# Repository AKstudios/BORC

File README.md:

# BORC
Battery-Operated Radiator Control

A low-power automatic radiator control that is designed to retrofit on steam radiators that use Honeywell's T104A1040 Zone Valve Operator
uses LowPowerLab's [DualOptiboot](https://github.com/LowPowerLab/DualOptiboot) bootloader for the ATmega1284P.

This repo contains:
- PCB design files and schematic for control board, power board and LED board for the BORC.
- Firmware for a low-power radiator control node
- Logger script to get real-time current data from the BORC

---

### Logger script

The [logger script](https://github.com/AKstudios/BORC/blob/dev/logger/logger.py) enables capturing current usage data over the serial port on the BORC.

#### Prerequisites:
- [Pyserial](https://pypi.org/project/pyserial/)

#### Run:
Run the script using the following command over a command line interface:

```
python logger.py -c COM15 -n filename
```
(change COM port number and filename as needed)

#### Tips:
- The script automatically adds the .csv extension to the filename, so there's no need to include it in the arguments when running the script
- Use -h command to bring a help menu
- If the servo doesn't move in some areas, you can adjust the default min and max limits to the particular servo installed. The default limits should be set to where the servo is guaranteed to move, and beyond these limits, the servo will not respond.
- Default baudrate for the BORC is 115200.

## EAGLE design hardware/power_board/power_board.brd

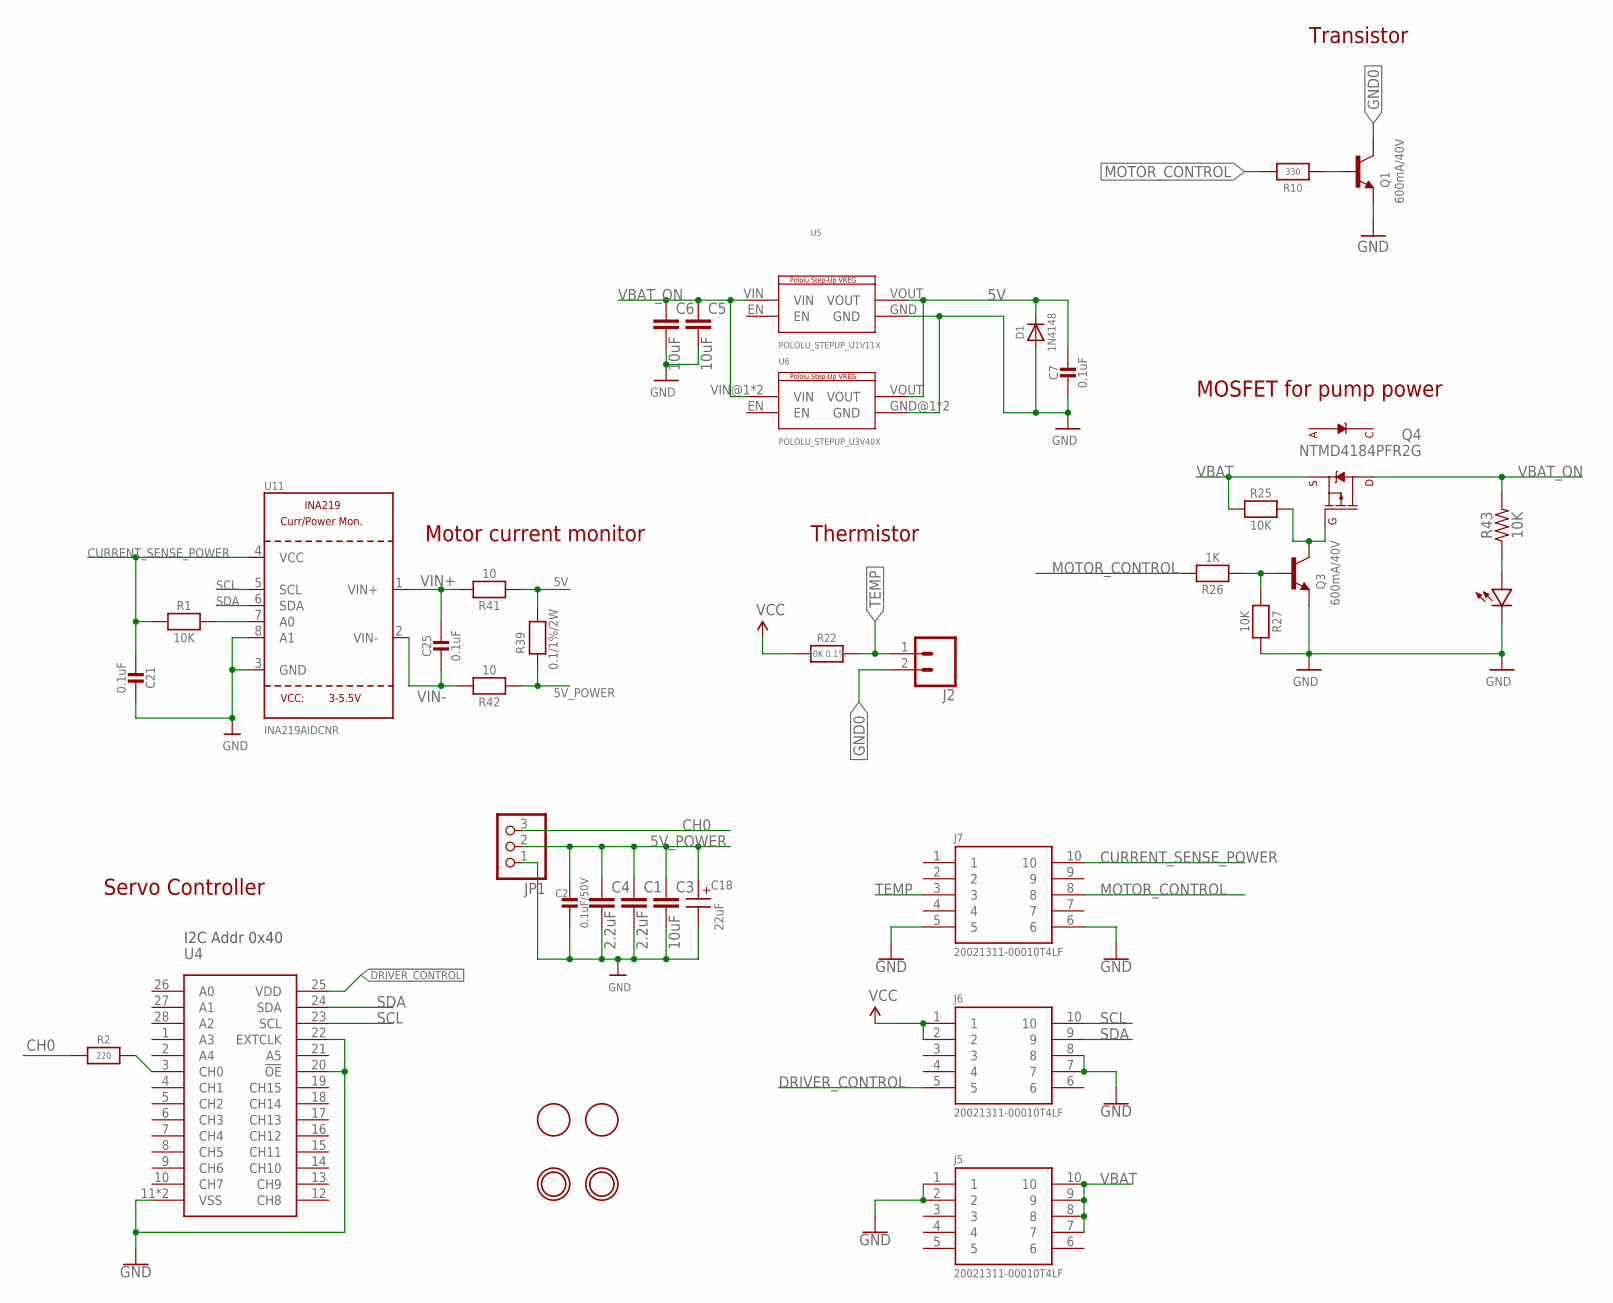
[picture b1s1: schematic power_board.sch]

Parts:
C1, C4: 2.2uF; 1206
C2: 0.1uF/50V; 0805-NO
C3: 10uF; 0805
C5, C6: 10uF; 1206
C7, C21, C25: 0.1uF; MICROBUILDER__0402MP; MPN GRM155R71C104KA88J
C18: 22uF; WCAP-ATLL_5X11(DXL); MPN 860160672011
D1: 1N4148; SOD-323; MPN 1N4148WX-TP
J2: CONN_02; 1X02
J5, J6, J7: 20021311-00010T4LF; HEADER_1.27MM_2X5
JP1: PINHD-1X3; 1X03
LED1: BLUE; 0805-LED; MPN 150080BS75000
Q1, Q3: 600mA/40V; SOT23-3; MPN MMBT3904-TP
Q4: NTMD4184PFR2G; SOIC-8; MPN NTMD4184PFR2G
R1, R25, R27: 10K; MICROBUILDER__0402MP; MPN RC0402FR-7W10KL
R2: 220; MICROBUILDER__0402MP; MPN RC0402JR-071KL
R10: 330; MICROBUILDER__0402MP; MPN RC0402JR-0710KL
R22: 10K 0.1%; MICROBUILDER__0402MP; MPN RC0402JR-0727RL
R26: 1K; MICROBUILDER__0402MP; MPN RC0402FR-101KL
R39: 0.1/1%/2W; 2512; MPN RCWE2512R100FKEA
R41, R42: 10; MICROBUILDER__0402MP; MPN RC0402FR-0710RL
R43: 10K; 0805; MPN RK73B2ATTD103J
U4: PCA9685HVQFN28; HVQFN28_SOT788-1
U5: POLOLU_STEPUP_U1V11X
U6: POLOLU_STEPUP_U3V40X
U11: INA219AIDCNR; SOT23-8; MPN INA219AIDCNR
U$2, U$3: MOUNTINGHOLE2.5; MOUNTINGHOLE_2.5_PLATED
U$8, U$9: FIDUCIAL; FIDUCIAL_1MM

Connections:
5V: C7.1, D1.C, R39.2, R41.1, U5.VOUT, U6.VOUT
5V_POWER: C1.1, C2.1, C3.1, C4.1, C18.1 (+), JP1.2, R39.1, R42.1
CH0: JP1.3, R2.1
CURRENT_SENSE_POWER: C21.2, J7.10, R1.1, U11.4 (VCC)
DRIVER_CONTROL: J6.5, U4.25 (VDD)
GND: C1.2, C2.2, C3.2, C4.2, C5.2, C6.2, C7.2, C18.2 (-), C21.1, D1.A, J5.1, J5.2, J6.7, J6.8, J7.5, J7.6, JP1.1, LED1.MINUS, Q1.2 (E), Q3.2 (E), R27.2, U4.11 (VSS), U4.20 (!OE), U4.22 (EXTCLK), U4.TH (VSS), U5.GND, U6.GND@1 (GND), U6.GND@2 (GND), U11.3 (GND), U11.8 (A1)
GND0: J2.2, Q1.3 (C)
MOTOR_CONTROL: J7.8, R10.2, R26.2
unnamed: R1.2, U11.7 (A0)
unnamed: Q1.1 (B), R10.1
unnamed: R2.2, U4.3 (CH0)
unnamed: LED1.PLUS, R43.1
unnamed: Q3.3 (C), Q4.4 (G), R25.2
unnamed: Q3.1 (B), R26.1, R27.1
SCL: J6.10, U4.23 (SCL), U11.5 (SCL)
SDA: J6.9, U4.24 (SDA), U11.6 (SDA)
TEMP: J2.1, J7.3, R22.2
VBAT: J5.7, J5.8, J5.9, J5.10, Q4.3 (S), R25.1
VBAT_ON: C5.1, C6.1, Q4.5 (D), Q4.6 (D), R43.2, U5.VIN, U6.VIN@1 (VIN), U6.VIN@2 (VIN)
VCC: J6.1, J6.2, R22.1
VIN+: C25.1, R41.2, U11.1 (VIN+)
VIN-: C25.2, R42.2, U11.2 (VIN-)

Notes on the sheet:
MOSFET for pump power
Motor current monitor
Thermistor
Transistor
I2C Addr 0x40
Servo Controller

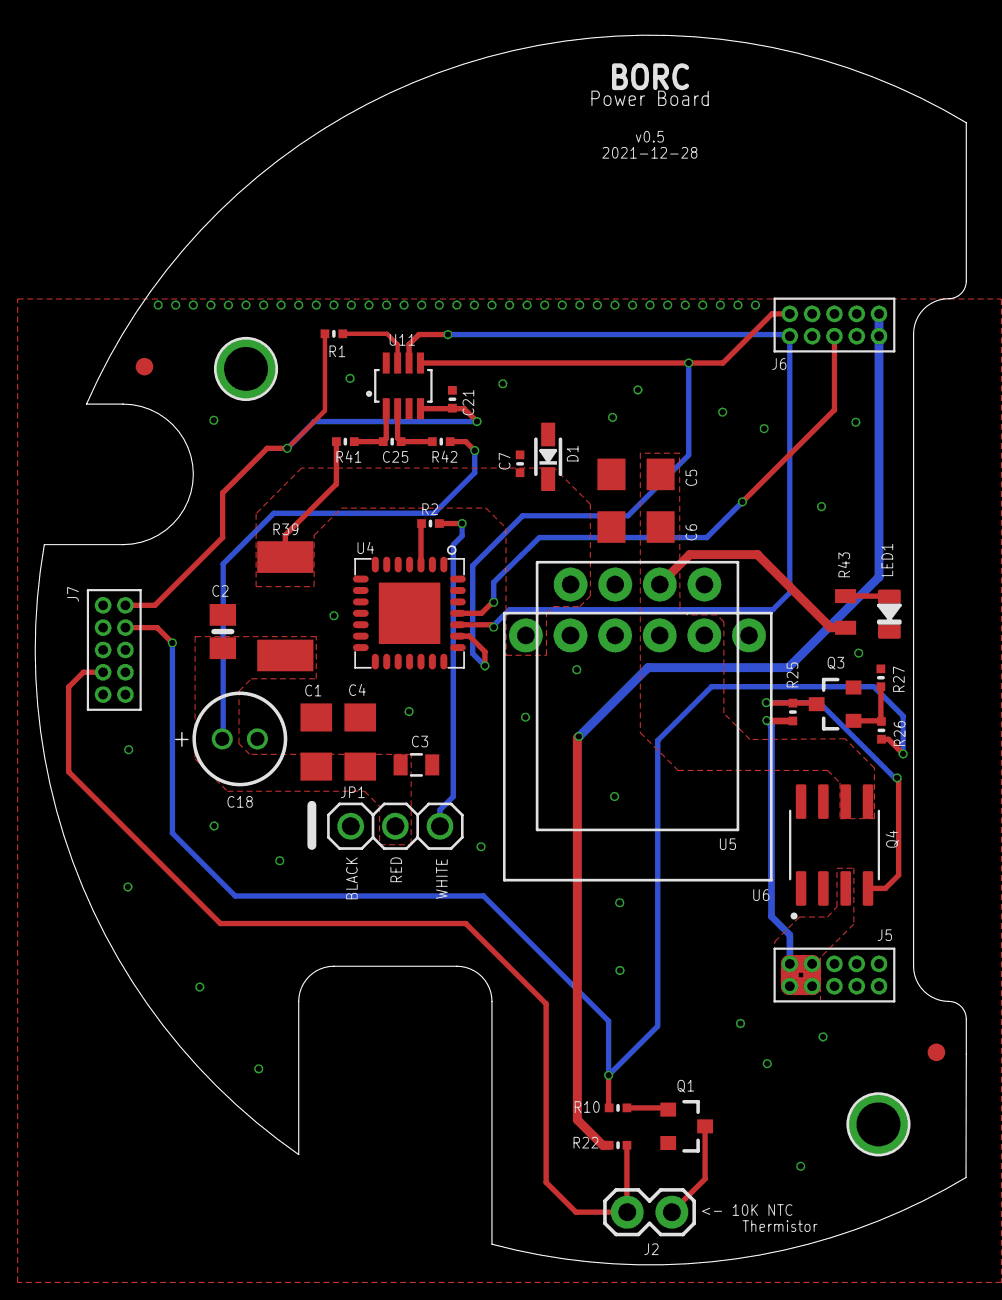
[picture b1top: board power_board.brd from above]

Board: 2 copper layers, 53.0 x 70.0 mm, 39 parts (0 on the bottom side), 22 nets.

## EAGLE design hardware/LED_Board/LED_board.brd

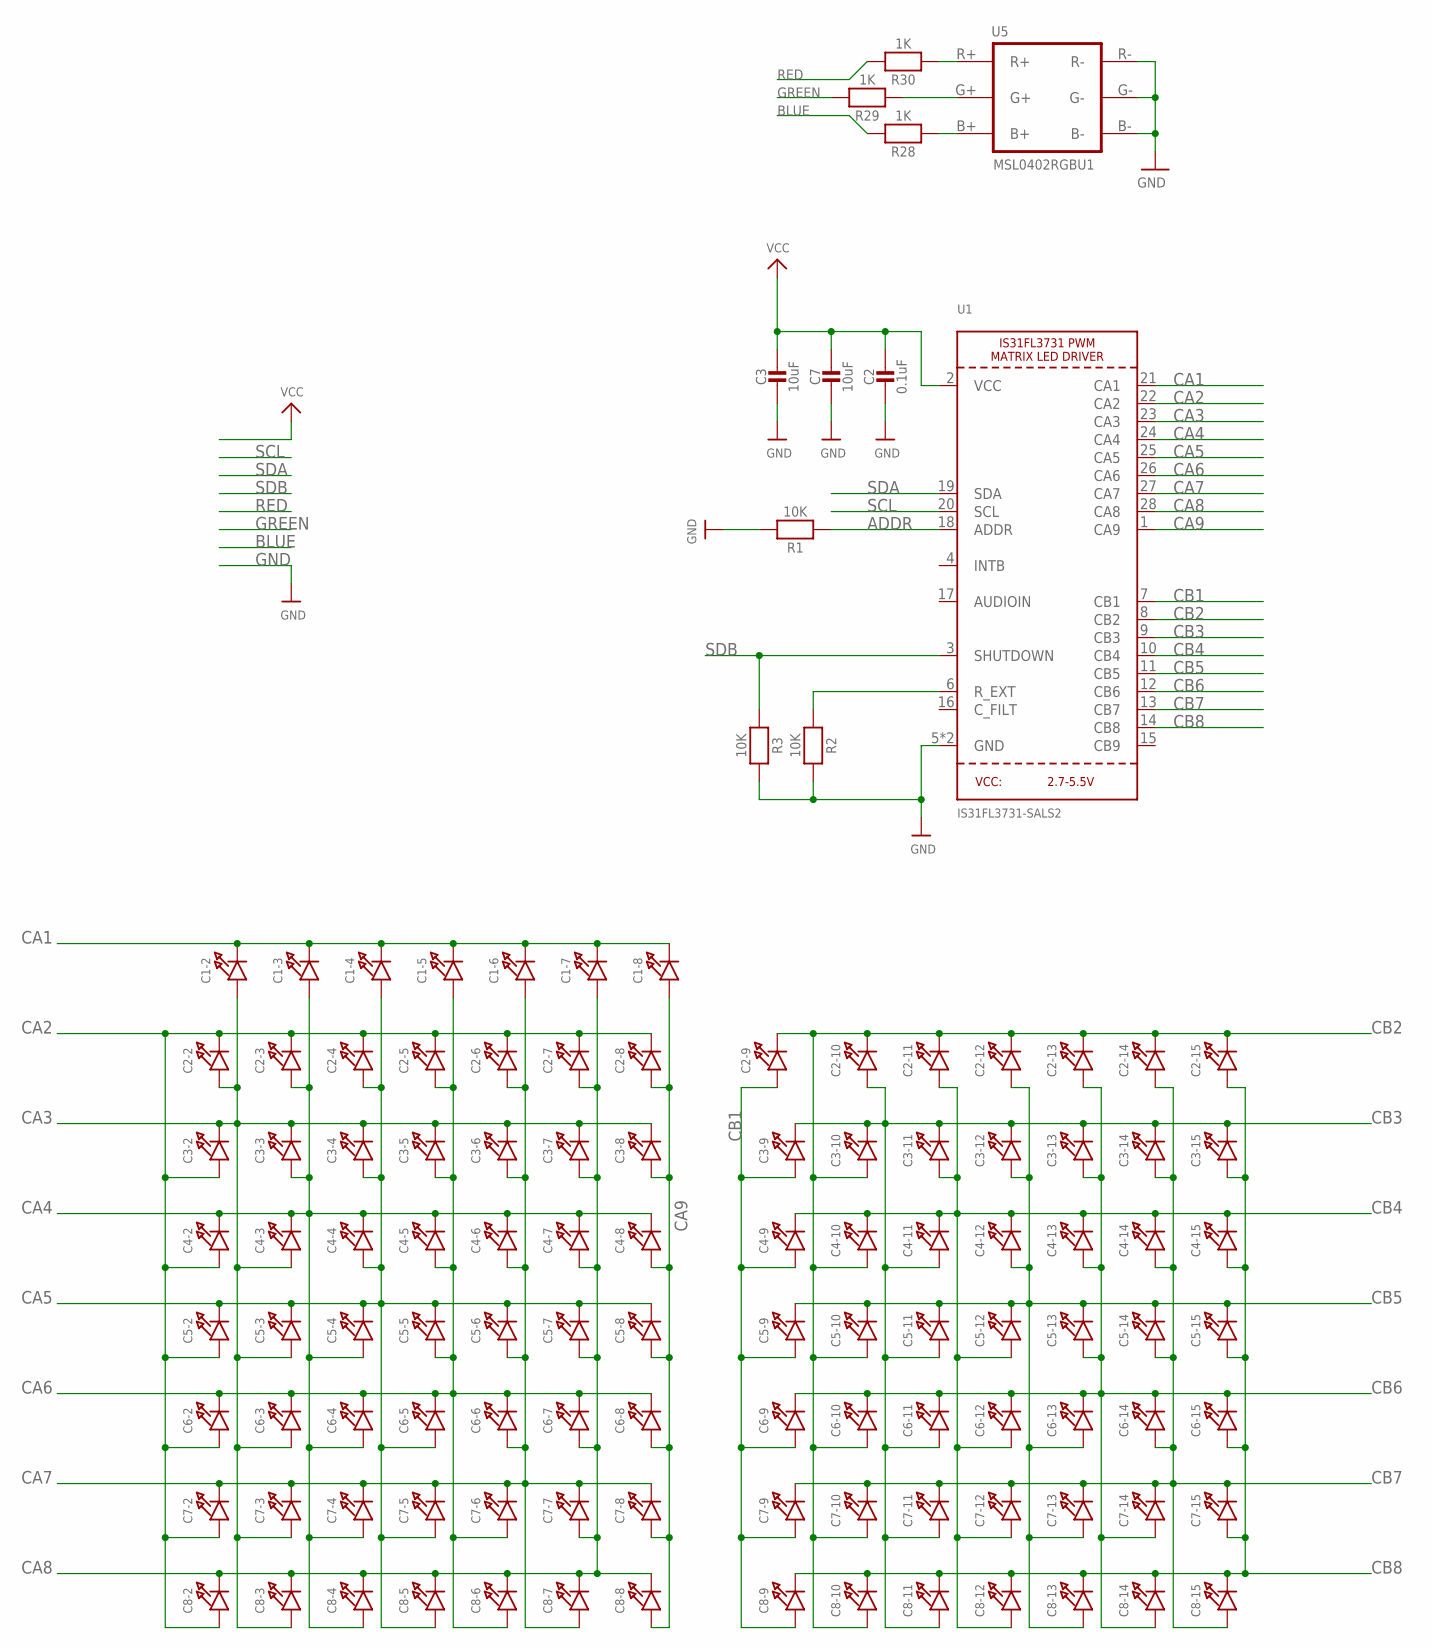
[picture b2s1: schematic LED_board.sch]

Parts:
C1-2, C1-3, C1-4, C1-5, C1-6, C1-7, C1-8, C2-2, C2-3, C2-4, C2-5, C2-6, C2-7, C2-8, C2-9, C2-10, C2-11, C2-12, C2-13, C2-14, C2-15, C3-2, C3-3, C3-4, C3-5, C3-6, C3-7, C3-8, C3-9, C3-10, C3-11, C3-12, C3-13, C3-14, C3-15, C4-2, C4-3, C4-4, C4-5, C4-6, C4-7, C4-8, C4-9, C4-10, C4-11, C4-12, C4-13, C4-14, C4-15, C5-2, C5-3, C5-4, C5-5, C5-6, C5-7, C5-8, C5-9, C5-10, C5-11, C5-12, C5-13, C5-14, C5-15, C6-2, C6-3, C6-4, C6-5, C6-6, C6-7, C6-8, C6-9, C6-10, C6-11, C6-12, C6-13, C6-14, C6-15, C7-2, C7-3, C7-4, C7-5, C7-6, C7-7, C7-8, C7-9, C7-10, C7-11, C7-12, C7-13, C7-14, C7-15, C8-2, C8-3, C8-4, C8-5, C8-6, C8-7, C8-8, C8-9, C8-10, C8-11, C8-12, C8-13, C8-14, C8-15: LED0603_NOOUTLINE; CHIPLED_0603_NOOUTLINE
C2: 0.1uF; MICROBUILDER__0402MP; MPN GRM155R71C104KA88J
C3, C7: 10uF; MICROBUILDER__0402MP; MPN GRM155R71C104KA88J
R1, R2, R3: 10K; MICROBUILDER__0402MP; MPN RC0402FR-7W10KL
R28, R29, R30: 1K; MICROBUILDER__0402MP; MPN RC0402FR-7W10KL
U1: IS31FL3731-SALS2; QFN28_4MM_0.4MM
U5: MSL0402RGBU1; SMD-6; MPN MSL0402RGBU1

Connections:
ADDR: R1.1, U1.18 (ADDR)
BLUE: R28.2
CA1: C1-2.C, C1-3.C, C1-4.C, C1-5.C, C1-6.C, C1-7.C, C1-8.C, U1.21 (CA1)
CA2: C2-2.C, C2-3.C, C2-4.C, C2-5.C, C2-6.C, C2-7.C, C2-8.C, C3-2.A, C4-2.A, C5-2.A, C6-2.A, C7-2.A, C8-2.A, U1.22 (CA2)
CA3: C1-2.A, C2-2.A, C3-2.C, C3-3.C, C3-4.C, C3-5.C, C3-6.C, C3-7.C, C3-8.C, C4-3.A, C5-3.A, C6-3.A, C7-3.A, C8-3.A, U1.23 (CA3)
CA4: C1-3.A, C2-3.A, C3-3.A, C4-2.C, C4-3.C, C4-4.C, C4-5.C, C4-6.C, C4-7.C, C4-8.C, C5-4.A, C6-4.A, C7-4.A, C8-4.A, U1.24 (CA4)
CA5: C1-4.A, C2-4.A, C3-4.A, C4-4.A, C5-2.C, C5-3.C, C5-4.C, C5-5.C, C5-6.C, C5-7.C, C5-8.C, C6-5.A, C7-5.A, C8-5.A, U1.25 (CA5)
CA6: C1-5.A, C2-5.A, C3-5.A, C4-5.A, C5-5.A, C6-2.C, C6-3.C, C6-4.C, C6-5.C, C6-6.C, C6-7.C, C6-8.C, C7-6.A, C8-6.A, U1.26 (CA6)
CA7: C1-6.A, C2-6.A, C3-6.A, C4-6.A, C5-6.A, C6-6.A, C7-2.C, C7-3.C, C7-4.C, C7-5.C, C7-6.C, C7-7.C, C7-8.C, C8-7.A, U1.27 (CA7)
CA8: C1-7.A, C2-7.A, C3-7.A, C4-7.A, C5-7.A, C6-7.A, C7-7.A, C8-2.C, C8-3.C, C8-4.C, C8-5.C, C8-6.C, C8-7.C, C8-8.C, U1.28 (CA8)
CA9: C1-8.A, C2-8.A, C3-8.A, C4-8.A, C5-8.A, C6-8.A, C7-8.A, C8-8.A, U1.1 (CA9)
CB1: C2-9.A, C3-9.A, C4-9.A, C5-9.A, C6-9.A, C7-9.A, C8-9.A, U1.7 (CB1)
CB2: C2-9.C, C2-10.C, C2-11.C, C2-12.C, C2-13.C, C2-14.C, C2-15.C, C3-10.A, C4-10.A, C5-10.A, C6-10.A, C7-10.A, C8-10.A, U1.8 (CB2)
CB3: C2-10.A, C3-9.C, C3-10.C, C3-11.C, C3-12.C, C3-13.C, C3-14.C, C3-15.C, C4-11.A, C5-11.A, C6-11.A, C7-11.A, C8-11.A, U1.9 (CB3)
CB4: C2-11.A, C3-11.A, C4-9.C, C4-10.C, C4-11.C, C4-12.C, C4-13.C, C4-14.C, C4-15.C, C5-12.A, C6-12.A, C7-12.A, C8-12.A, U1.10 (CB4)
CB5: C2-12.A, C3-12.A, C4-12.A, C5-9.C, C5-10.C, C5-11.C, C5-12.C, C5-13.C, C5-14.C, C5-15.C, C6-13.A, C7-13.A, C8-13.A, U1.11 (CB5)
CB6: C2-13.A, C3-13.A, C4-13.A, C5-13.A, C6-9.C, C6-10.C, C6-11.C, C6-12.C, C6-13.C, C6-14.C, C6-15.C, C7-14.A, C8-14.A, U1.12 (CB6)
CB7: C2-14.A, C3-14.A, C4-14.A, C5-14.A, C6-14.A, C7-9.C, C7-10.C, C7-11.C, C7-12.C, C7-13.C, C7-14.C, C7-15.C, C8-15.A, U1.13 (CB7)
CB8: C2-15.A, C3-15.A, C4-15.A, C5-15.A, C6-15.A, C7-15.A, C8-9.C, C8-10.C, C8-11.C, C8-12.C, C8-13.C, C8-14.C, C8-15.C, U1.14 (CB8)
GND: C2.2, C3.2, C7.2, R1.2, R2.2, R3.2, U1.5 (GND), U1.THERMAL (GND), U5.B-, U5.G-, U5.R-
GREEN: R29.2
unnamed: R28.1, U5.B+
unnamed: R30.1, U5.R+
unnamed: R29.1, U5.G+
RED: R30.2
R_EXT: R2.1, U1.6 (R_EXT)
SCL: U1.20 (SCL)
SDA: U1.19 (SDA)
SDB: R3.1, U1.3 (SHUTDOWN)
VCC: C2.1, C3.1, C7.1, U1.2 (VCC)

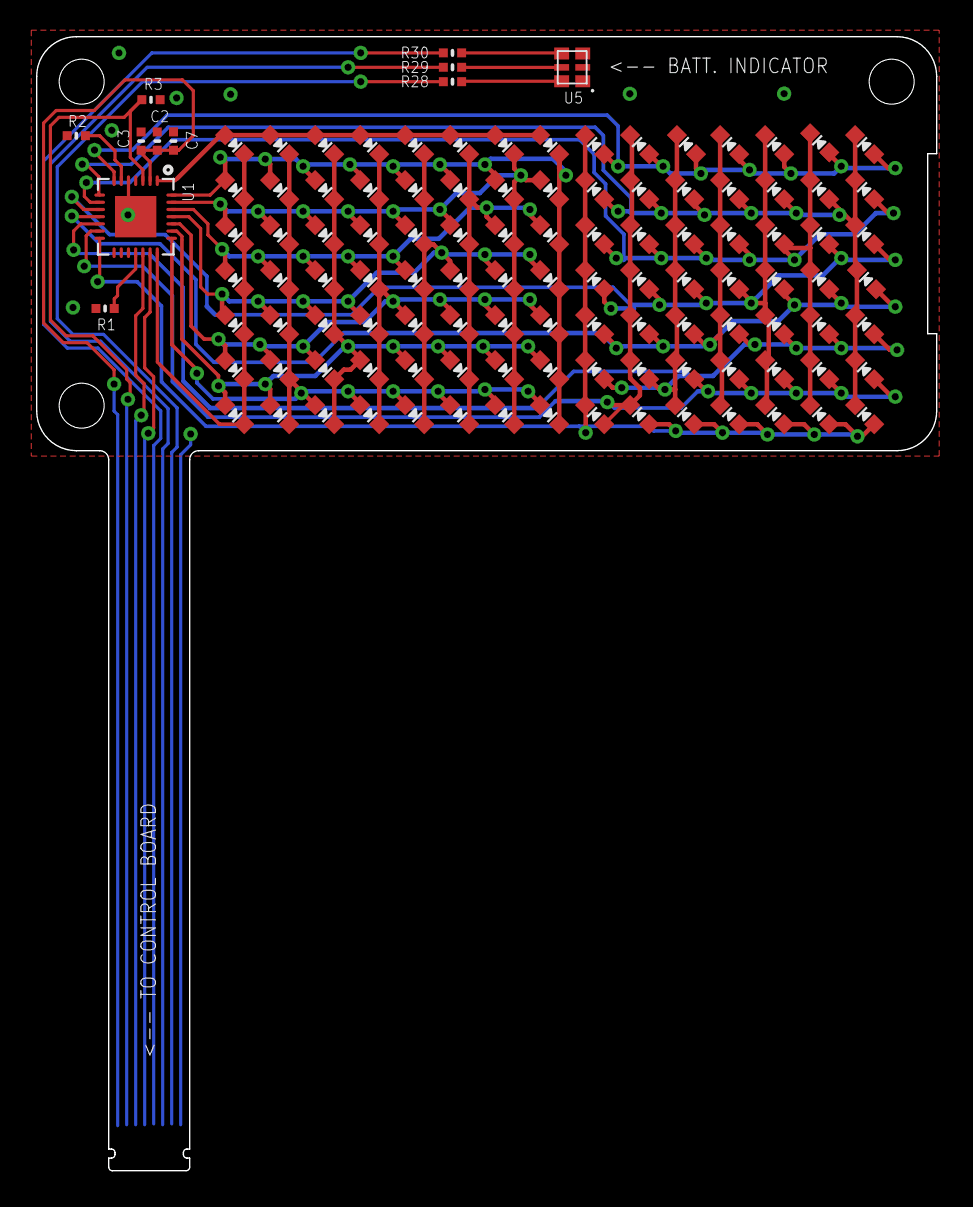
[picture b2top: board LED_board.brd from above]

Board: 2 copper layers, 50.0 x 63.0 mm, 116 parts (0 on the bottom side), 25 nets.

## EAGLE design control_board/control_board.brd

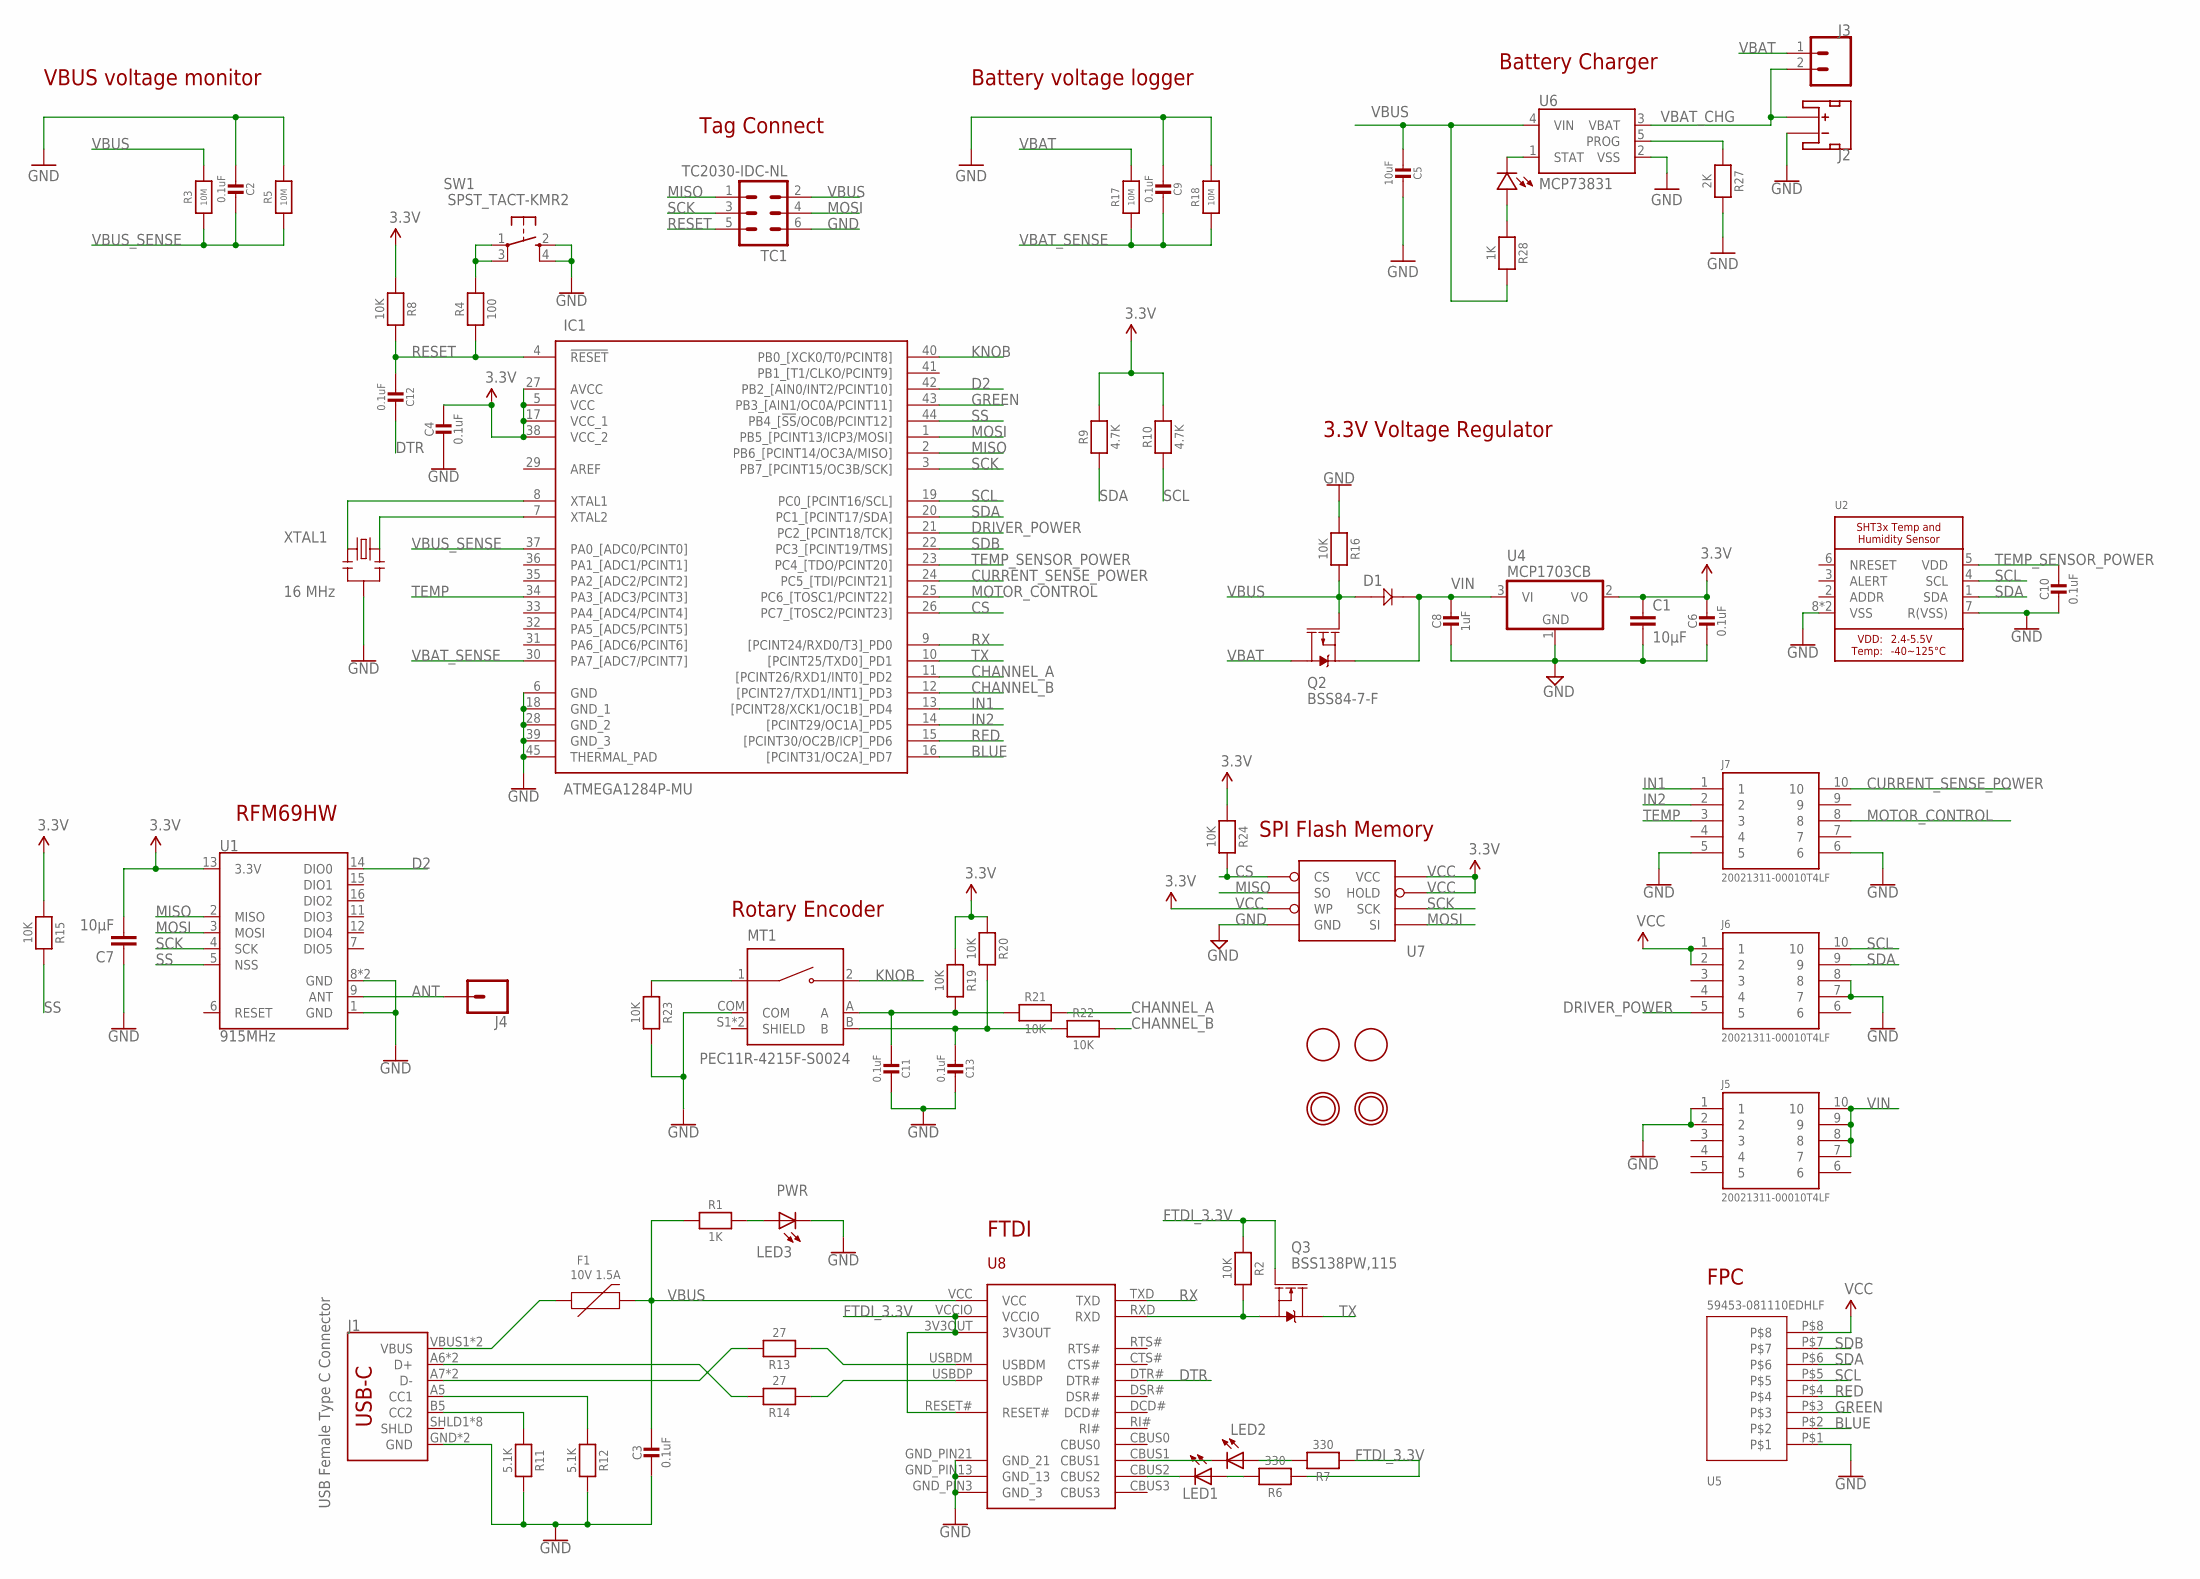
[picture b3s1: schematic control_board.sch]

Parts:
C1, C7: 10µF; 0805
C2, C3, C4, C6, C9, C10, C11, C12, C13: 0.1uF; MICROBUILDER__0402MP; MPN GRM155R71C104KA88J
C5: 10uF; MICROBUILDER__0402MP; MPN GRM155R71C104KA88J
C8: 1uF; MICROBUILDER__0402MP; MPN GRM155R71C104KA88J
D1: DIODE_SCHOTTKY0805-RES; 0805
F1: 10V 1.5A; 0805; MPN MF-PSML110-2
IC1: ATMEGA1284P-MU; QFN50P700X700X100-45N
J1: USB Female Type C Connector; USB-C-16P
J2: JST_2MM_MALE; JST-2-SMD
J3: CONN_02; 1X02
J4: CONN_01; 1X01
J5, J6, J7: 20021311-00010T4LF; HEADER_1.27MM_2X5
LED1, LED2: LEDCHIPLED_0603; CHIPLED_0603
LED3: PWR; CHIPLED_0603
LED4: LED0603; 0603-LED
MT1: PEC11R-4215F-S0024; XDCR_PEC11R-4215F-S0024
Q2: BSS84-7-F; SOT23-3
Q3: BSS138PW,115; SOT323
R1, R28: 1K; MICROBUILDER__0402MP; MPN RC0402FR-7W10KL
R2, R8, R15, R16, R19, R20, R21, R22, R23, R24: 10K; MICROBUILDER__0402MP; MPN RC0402FR-7W10KL
R3, R5, R17, R18: 10M; MICROBUILDER__0402MP; MPN RC0402JR-0710KL
R4: 100; MICROBUILDER__0402MP; MPN RC0402FR-7W10KL
R6, R7: 330; MICROBUILDER__0402MP; MPN RC0402FR-7W10KL
R9, R10: 4.7K; MICROBUILDER__0402MP; MPN RC0402FR-7W10KL
R11, R12: 5.1K; MICROBUILDER__0402MP; MPN RC0402FR-7W10KL
R13, R14: 27; MICROBUILDER__0402MP; MPN RC0402FR-7W10KL
R27: 2K; MICROBUILDER__0402MP; MPN RC0402FR-7W10KL
SW1: SPST_TACT-KMR2; KMR2
TC1: TC2030-IDC-NL
U1: 915MHz; RFM69HCW-XXXS2
U2: SHT3X
U4: MCP1703CB; SOT23
U5: 59453-081110EDHLF
U6: MCP73831; SOT23-5
U7: AT25F512BJEDEC_3.9MM; SO08
U8: FT231XQ-R; FTDI_FT231XQ-R_PACKAGE
U$2, U$3: MOUNTINGHOLE2.5; MOUNTINGHOLE_2.5_PLATED
U$8, U$9: FIDUCIAL; FIDUCIAL_1MM
XTAL1: 16 MHz; RESONATOR-SMD

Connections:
A: C11.2, MT1.A, R19.2, R21.1
ANT: J4.1, U1.9 (ANT)
B: C13.2, MT1.B, R20.2, R22.1
BLUE: IC1.16 ([PCINT31/OC2A]_PD7), U5.P$2
CHANNEL_A: IC1.11 ([PCINT26/RXD1/INT0]_PD2), R21.2
CHANNEL_B: IC1.12 ([PCINT27/TXD1/INT1]_PD3), R22.2
CS: IC1.26 (PC7_[TOSC2/PCINT23]), R24.2, U7.1_CS (CS)
CURRENT_SENSE_POWER: IC1.24 (PC5_[TDI/PCINT21]), J7.10
D2: IC1.42 (PB2_[AIN0/INT2/PCINT10]), U1.14 (DIO0)
DRIVER_POWER: IC1.21 (PC2_[PCINT18/TCK]), J6.5
DTR: C12.1, U8.DTR#
FTDI_3.3V: Q3.1 (G), R2.1, R6.1, R7.1, U8.3V3OUT, U8.RESET#, U8.VCCIO
GND: C1.2, C2.2, C3.2, C4.2, C5.1, C6.2, C7.1, C8.2, C9.2, C10.2, C11.1, C13.1, IC1.6 (GND), IC1.18 (GND_1), IC1.28 (GND_2), IC1.39 (GND_3), IC1.45 (THERMAL_PAD), J1.GND, J1.GND2 (GND), J2.1 (-), J5.1, J5.2, J6.7, J6.8, J7.5, J7.6, LED3.C, MT1.COM, R5.2, R11.2, R12.2, R16.1, R18.2, R23.2, R27.2, SW1.2 (S), SW1.4 (S1), TC1.6, U1.1 (GND), U1.8 (GND), U1.10 (GND), U2.7 (R(VSS)), U2.8 (VSS), U2.THERMAL (VSS), U4.1 (GND), U5.P$1, U6.2 (VSS), U7.4_GND (GND), U8.GND_PIN3 (GND_3), U8.GND_PIN13 (GND_13), U8.GND_PIN21 (GND_21), XTAL1.2
GREEN: IC1.43 (PB3_[AIN1/OC0A/PCINT11]), U5.P$3
IN1: IC1.13 ([PCINT28/XCK1/OC1B]_PD4), J7.1
IN2: IC1.14 ([PCINT29/OC1A]_PD5), J7.2
KNOB: IC1.40 (PB0_[XCK0/T0/PCINT8]), MT1.2
MISO: IC1.2 (PB6_[PCINT14/OC3A/MISO]), TC1.1, U1.2 (MISO), U7.2_SO (SO)
MOSI: IC1.1 (PB5_[PCINT13/ICP3/MOSI]), TC1.4, U1.3 (MOSI), U7.5_SI (SI)
MOTOR_CONTROL: IC1.25 (PC6_[TOSC1/PCINT22]), J7.8
unnamed: IC1.8 (XTAL1), XTAL1.1
unnamed: LED3.A, R1.2
unnamed: IC1.7 (XTAL2), XTAL1.3
unnamed: J1.B5 (CC2), R11.1
unnamed: J1.A5 (CC1), R12.1
unnamed: J1.A6 (D+), J1.B6 (D+), R14.2
unnamed: J1.A7 (D-), J1.B7 (D-), R13.2
unnamed: R14.1, U8.USBDP
unnamed: R13.1, U8.USBDM
unnamed: F1.1, J1.VBUS1 (VBUS), J1.VBUS2 (VBUS)
unnamed: MT1.1, R23.1
unnamed: R4.2, SW1.1, SW1.3 (P1)
unnamed: LED1.C, U8.CBUS2
unnamed: Q3.2 (S), R2.2, U8.RXD
unnamed: LED1.A, R6.2
unnamed: LED4.PLUS, R28.1
unnamed: LED2.A, R7.2
unnamed: LED2.C, U8.CBUS1
unnamed: LED4.MINUS, U6.1 (STAT)
PROG1: R27.1, U6.5 (PROG)
RED: IC1.15 ([PCINT30/OC2B/ICP]_PD6), U5.P$4
RESET: C12.2, IC1.4 (!RESET), R4.1, R8.2, TC1.5
RX: IC1.9 ([PCINT24/RXD0/T3]_PD0), U8.TXD
SCK: IC1.3 (PB7_[PCINT15/OC3B/SCK]), TC1.3, U1.4 (SCK), U7.6_SCK (SCK)
SCL: IC1.19 (PC0_[PCINT16/SCL]), J6.10, R10.1, U2.4 (SCL), U5.P$5
SDA: IC1.20 (PC1_[PCINT17/SDA]), J6.9, R9.1, U2.1 (SDA), U5.P$6
SDB: IC1.22 (PC3_[PCINT19/TMS]), U5.P$7
SS: IC1.44 (PB4_[!SS!/OC0B/PCINT12]), R15.2, U1.5 (NSS)
TEMP: IC1.34 (PA3_[ADC3/PCINT3]), J7.3
TEMP_SENSOR_POWER: C10.1, IC1.23 (PC4_[TDO/PCINT20]), U2.5 (VDD)
TX: IC1.10 ([PCINT25/TXD0]_PD1), Q3.3 (D)
VBAT: J3.1, Q2.3 (D1), R17.2
VBAT_CHG: J2.2 (+), J3.2, U6.3 (VBAT)
VBAT_SENSE: C9.1, IC1.30 (PA7_[ADC7/PCINT7]), R17.1, R18.1
VBUS: C3.1, C5.2, D1.1, F1.2, Q2.1 (G1), R1.1, R3.2, R16.2, R28.2, TC1.2, U6.4 (VIN), U8.VCC
VBUS_SENSE: C2.1, IC1.37 (PA0_[ADC0/PCINT0]), R3.1, R5.1
VCC: C1.1, C4.1, C6.1, C7.2, IC1.5 (VCC), IC1.17 (VCC_1), IC1.27 (AVCC), IC1.38 (VCC_2), J6.1, J6.2, R8.1, R9.2, R10.2, R15.1, R19.1, R20.1, R24.1, U1.13 (3.3V), U4.2 (VO), U5.P$8, U7.3_WP (WP), U7.7_HOLD (HOLD), U7.8_VCC (VCC)
VIN: C8.1, D1.2, J5.7, J5.8, J5.9, J5.10, Q2.2 (S1), U4.3 (VI)

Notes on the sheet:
Battery Charger
Battery voltage logger
3.3V Voltage Regulator
SPI Flash Memory
Rotary Encoder
Tag Connect
RFM69HW
FTDI
FPC
VBUS voltage monitor

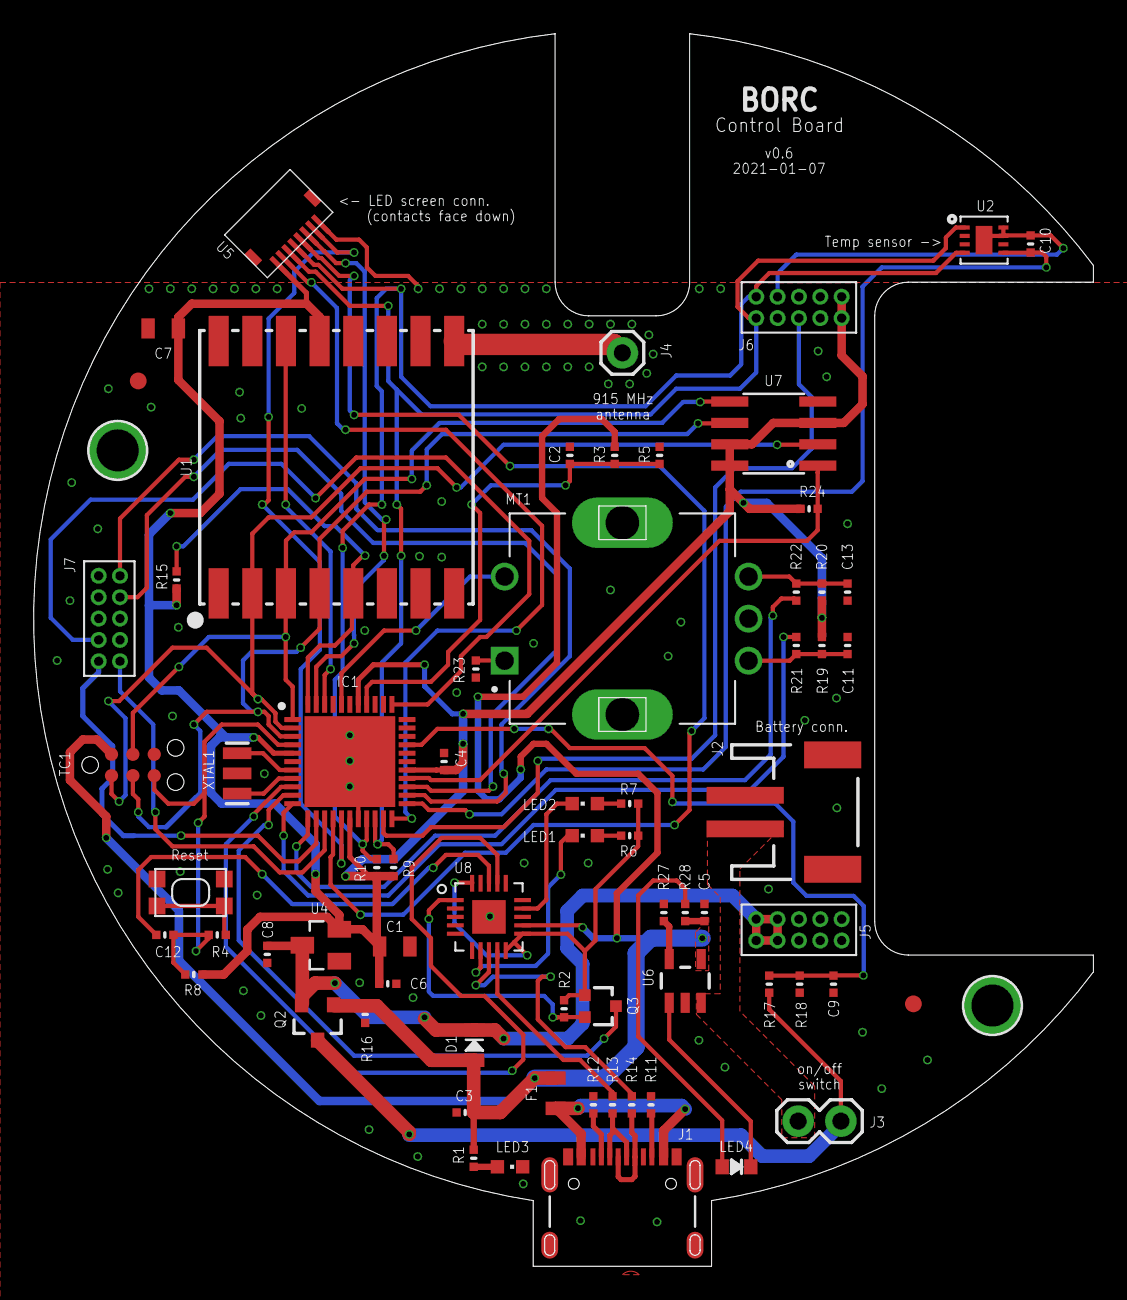
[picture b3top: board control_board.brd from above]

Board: 2 copper layers, 63.0 x 73.3 mm, 70 parts (0 on the bottom side), 58 nets.

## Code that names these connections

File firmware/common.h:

#ifndef _COMMON_H_
#define _COMMON_H_
#include <stdint.h>


// Set to 1 for compiling on systems with very limited hardware
#define NO_HW 0

// system mode
enum mode_t : uint8_t
{
    MANUAL_MODE   = 0,
    MENU_MODE     = 1,
    SETPOINT_MODE = 2
};

// servo calibration mode
enum servocal_t : uint8_t
{
    NOTCAL = 0,
    CAL = 1,
    DONTCAL = 2
};

// radio packet type
enum packet_type_t  : uint8_t
{
    CONFIG_PACKET       = 0,
    TELEMETRY_PACKET    = 1,
    RESPONSE_PACKET     = 2
};

// Number of seconds that define a hardware-sleep period (base time = 32 secs)
#define SLEEP_TIME_SECS 32

// Misc. global variables ------------------------------------------
#define SERIAL_BAUD               115200

// I2C Addresses ---------------------------------------------------

#if NO_HW
  #define CURRENT_SENSE_ADDRESS   0x40
  #define TEMP_SENSE_ADDRESS      0x44
  #define SERVO_DRIVER_ADDRESS    0x00
  #define LED_MATRIX_ADDRESS      0x74
#else
  #define CURRENT_SENSE_ADDRESS   0x41  
  #define TEMP_SENSE_ADDRESS      0x45  
  #define SERVO_DRIVER_ADDRESS    0x40
  #define LED_MATRIX_ADDRESS      0x74
#endif



// Pin mapping -----------------------------------------------------
#define CLICK_PIN                 0
#define GREEN_PIN                 3
#define CHANNEL_B                 10
#define CHANNEL_A                 11
#define RED_PIN                   14
#define BLUE_PIN                  15
#define DRIVER_POWER_PIN          18
#define LED_SCREEN_POWER_PIN      19
#define TEMP_SENSOR_POWER_PIN     20
#define CURRENT_SENSE_POWER_PIN   21
#define SERVO_POWER_PIN           22
#define FLASH_SS                  23
#define VBUS_SENSE                A0
#define TEMP_SENSE                A3
#define VBAT_SENSE                A7

// Define error code bits ------------------------------------------
#define BATT_ERR                  (1 << 0)   // battery low/bad voltage
#define TEMP_SENSE_ERR            (1 << 1)   // temp sensor not working
#define LED_DRV_ERR               (1 << 2)   // LED driver not working
#define CURRENT_SENSE_ERR         (1 << 3)   // current sensor not working
#define SERVO_POWER_ERR           (1 << 4)   // servo voltage not correct
#define FLASH_ERR                 (1 << 5)   // SPI flash error
#define RADIO_ERR                 (1 << 6)   // Radio error
#define SERVO_ERR                 (1 << 7)   // servo error (didn't move)


#endif

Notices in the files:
parts and their libraries:
SparkFun-RF: Licensing: Creative Commons ShareAlike 4.0 International - https://creativecommons.org/licenses/by-sa/4.0
microbuilder: This work is placed in the public domain, and may be freely used for commercial and non-commercial work with the following conditions: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
